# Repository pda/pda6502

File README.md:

pda6502
=======

pda6502 is a home-built computer powered by an 8-bit [6502][6502] CPU
([WDC 65C02][65C02]), varitions of which powered the venerable Commodore 64,
Apple II, Vic 20, Nintendo and lots more.

[74HC-series][7400] logic chips map the 64K address space to 32K RAM, 8K ROM, a
[6522 VIA I/O controller][6522], and room for expansion.

The first output device (beyond flashing LEDs) is a [128x32 pixel OLED][oled],
connected to one of the VIA 6522 parallel ports, with bit-banged serial comms.

It's currently exclusively running the 6502 assembly code which I've written in
the `src/` directory of this project. As of April 2014, it can bit-bang SPI on
the VIA parallel ports to drive the OLED display, rendering text using the old
Commodore 64 font data.

The code is assembled with [ca65][ca65], part of the [cc65][cc65] 6502
development package.

Notes
-----

ILI9340 SPI performance; filling 200x200 square.
baseline: 4.5 seconds.

Emulator
--------

I've also written [go6502][go6502], an emulator for this system.

go6502 features a stepping debugger with breakpoints on instruction type,
register values and memory location. This makes it far easier to get code
working correctly before writing it to an actual EEPROM.

Address layout
--------------

Considerations:

* 6502 has 16-bit address bus; can address 64K memory.
* Zero-page (0x0000..0x00FF) must be RAM, used as external registers.
* Stack (0x0100..0x00FF) must be RAM.
* PC (program counter) is initialized from 0xFFFC, so must be ROM.
* 6522 VIA (I/O) has 4-bit RS (register select), needs 16 bytes mapped.
* AT28C64 EEPROMs are 8kb. I have some.
* Nice to have:
  * Fancy bank-switching (e.g. ROMs overlaying RAM, C64-style).
  * Different mapping for read vs. write, e.g. read ROM, write RAM.

74HC521/74HC688 can route a specific page (256 bytes, upper 8 bits of address)
to a destination. See http://wilsonminesco.com/6502primer/addr_decoding.html

So using the highest three pins of the address bus, the memory space
can be divided down to 8K blocks.

A simple RAM+ROM+IO scheme:
Allows for future extensions e.g. upper 32K RAM, with ROMs and I/O overlaid.

* 0x0000..0x7FFF: 32K RAM, uninterrupted. Contains zero-page and stack.
* 0x8000..0xBFFF: (reserved)
* 0xC000..0xCFFF: 4K I/O (initially only 16 bytes used by 6522 VIA)
* 0xD000..0xDFFF: (reserved)
* 0xE000..0xFFFF: 8K ROM ("kernal" [sic])

Address table for upper 3 bits of address bus:

NOTE: A15 can directly control RAM's CE/OE.
      This means a 74HC138 decoder can run on A12..14
      (With A15 as the '138 active-high enable input)

Address bus 4 KB chunks:

```
     High   Dec  Dec
Seg  Bits    In  Out  Base    Function
------------------------------------------------
  0  0000             0x0000  RAM
  1  0001             0x1000  RAM
  2  0010             0x2000  RAM
  3  0011             0x3000  RAM
  4  0100             0x4000  RAM
  5  0101             0x5000  RAM
  6  0110             0x6000  RAM
  7  0111             0x7000  RAM
  8  1000   000    0  0x8000
  9  1001   100    4  0x9000  IO (VIA) (should be at 0xC000)
  A  1010   010    2  0xA000
  B  1011   110    6  0xB000  ROM (KERNAL) (should be at 0xE000)
  C  1100   001    1  0xC000
  D  1101   101    5  0xD000
  E  1110   011    3  0xE000
  F  1111   111    7  0xF000  ROM (KERNAL)
```

* 74HC138 (3-to-8 decoder)
    * G1 (active-high enable) driven by A15 (only active 0x8000 and above)
    * G2 (active-low enable) permanently LOW/enabled.
    * Inputs A, B, C driven by A12, A13, A14.
    * Output Y4 enables VIA.
    * Output Y6 & Y7 drive KERNAL ROM via AND gate.
* 74HC08 (Quad 2-input AND gates)
    * Input A1, B1 from 74HC138 Y6, Y7, output Y1 to KERNAL ROM CE/OE.
    * Input A2, B2 from phase2, A15, output Y2 to RAM CS/OE.
    * Three spare AND gates.
* 74HC00 (Quad 2-input NAND gates)
    * Input A1, B1 from A15 (as inverter), output Y1 to A2.
    * Input A2, B2 from Y1, phase2 clock, output Y2 to RAM CS/OE.
* VIA 6522
    * CS1 permanently HIGH/active.
    * CS2B to 74HC138 Y4 (LOW/active for `0b1110____`).
    * Data 0..7 to data bus D0..7.
    * Address 0..3 to address bus A0..3.
    * RWB to 6502 RWB.
    * PHI2 to system oscillator, same as 6502.
    * RESB to reset button, same as 6502.
* ROM AT28C64
    * CE and OE both active-low, tied together.
    * CE/OE to 74HC08 Y1, (LOW/active for `0b111_____`)
    * WE permanently HIGH/inactive.
    * I/O 0..7 to data bus D0..7.
    * Address 0..12 to address bus A0..12.
* RAM (32Kx8 CMOS SRAM; UM61256AK-12)
    * CE and OE both active-low, tied together.
    * CE/OE driven by A15+phase2 via 74HC00 (LOW/active for `0b0_______`)
    * WE (active low) to 6502 RWB.
    * Address 0..14 to address bus A0..14.

Zero Page
---------

The zero page (`0x0000..0x00FF`) is frequently used as "external registers".

Note that Some 6502 derivatives dedicate the first few bytes to hardware ports and
control registers, best avoid those? e.g. 6510 in C64 uses at least two.

[6502]: http://en.wikipedia.org/wiki/MOS_Technology_6502
[65C02]: http://en.wikipedia.org/wiki/WDC_65C02
[6522]: http://en.wikipedia.org/wiki/MOS_Technology_6522
[7400]: http://en.wikipedia.org/wiki/List_of_7400_series_integrated_circuits
[oled]: https://www.adafruit.com/products/661
[golang]: http://golang.org/
[go6502]: https://github.com/pda/go6502
[ca65]: http://cc65.github.io/cc65/doc/ca65.html
[cc65]: http://cc65.github.io/cc65/

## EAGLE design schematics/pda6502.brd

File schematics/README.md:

pda6502 schematics
==================

Schematics for pda6502 hardware builds.

Disclaimer: I have no idea what I'm doing.

First iteration is aiming towards a core board for the 6502, 6522, ROM, RAM and
oscillator.  It would connect the power, data bus, address bus, reset lines and
clock lines.  All other functionality (including memory-mapping logic) would be
external via headers.

A 2x10 header exposes the 6522 VIA ports A and B and their control lines.

Notes / TODO
------------

ERRORS:

* A,B,C inputs to 74HC138 reversed!
    * Moves VIA from $C000 to $9000.
    * Moves lower half of kernal ROM from $E000 to $B000.
* 47uF cap footprint too small.
* reset button footprint too small.
* Expansion font too light for silkscreen printing.

Micro B USB socket:
Dangerous Prototypes Eagle library.
Device: CONN-USB-MICRO-B
USB micro-b connector SMT 0.65 mm pitch, 1.45mm from center to PCB edge, Based on TE part number 1981568-1
http://www.mouser.com/ProductDetail/TE-Connectivity-AMP/1981568-1/?qs=zxTme0yW/baAfvOKTKC5hw==

Memory mapping logic
--------------------

* IN:  CPU A12
* IN:  CPU A13
* IN:  CPU A14
* IN:  CPU A15
* IN:  CPU PHI2
* IN:  CPU PHI1O
* IN:  CPU RWB
* OUT: RAM OE+CE
* OUT: ROM OE+CE
* OUT: VIA CS2B

Logic chips:

* 74HC00 (quad NAND) acting as inverter, NAND gate, and AND gate.
* 74HC138 (3-bit decoder) to split the upper-half of address space.

Propagation times:

* 74HC00 gates: typical 8 ns, max 23 ns.
* 74HC138: typical 15 ns, max 38 ns.

* RAM: invert (NAND) + NAND = typical 16 ns, max 46 ns.
* VIA: 74HC138 = typical 15 ns, max 38 ns.
* ROM: 74HC138 + (NAND + NAND) = typical 31 ns, max 84 ns.

* RAM speed: 12 ns
* ROM speed: 250 ns or 120 ns? 150 ns for Atmel AT28C256-15

Power characteristics
---------------------

Designing for maximum of 1A current should be plenty:

[vreg]: http://www.mouser.com/Search/ProductDetail.aspx?R=MC7805CDTRKGvirtualkey58410000virtualkey863-MC7805CDTRKG

```
65C02: 12 mA @ 8 MHz; 1.5 mA per MHz supply current (loaded)
65C22:  4 mA @ 8 MHz; 0.5 mA per MHz supply current (loaded)
28C64: 30 mA max.
SRAM: 200 mA max; 80 mA typical
      ==========
      246 mA max (chips)
      ==========
TFT:  100 mA
uSD:  100 mA (max during writes)
xprot: 60 mA
oled:  20 mA
      ==========
      526 mA
      ==========
```

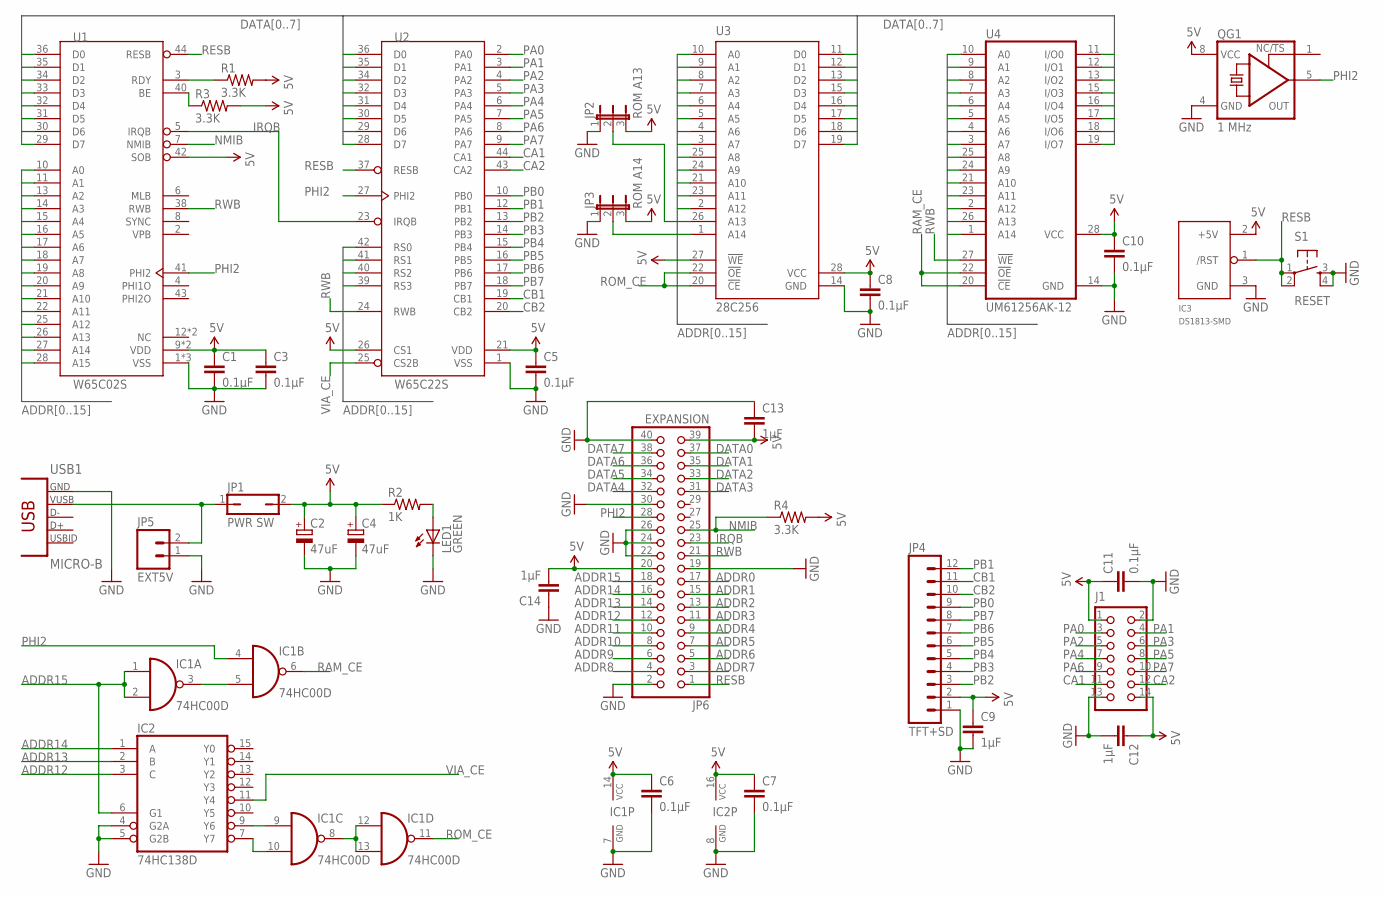
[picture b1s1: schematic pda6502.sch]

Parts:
C1, C3, C5, C6, C7, C8, C10, C11: 0.1μF; C0805
C2, C4: 47uF; CASE_B
C9, C12, C13, C14: 1μF; C0805
IC1: 74HC00D; SO14
IC2: 74HC138D; SO16
IC3: DS1813-SMD; SOT-23
J1: CON_HEADER_2X07-PTH; M2X7
JP1: PWR SW; JMP-1X2
JP2: ROM A13; JP2
JP3: ROM A14; JP2
JP4: TFT+SD; 1X12_NO_SILK_KIT
JP5: EXT5V; 1X02
JP6: EXPANSION; 2X20
LED1: GREEN; LED-805
QG1: 1 MHz; DIL08S
R1, R3, R4: 3.3K; R0805
R2: 1K; R0805
S1: RESET; TACTILE-SWITCH-SMD
U1: W65C02S; PLCC44-SOCKET
U2: W65C22S; PLCC44-SOCKET
U3: 28C256; ZIF28-6-WIDE
U4: UM61256AK-12; DIL28-3
USB1: MICRO-B; CONN_USB_MICRO-B

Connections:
5V: C1.1, C2.+, C3.1, C4.+, C5.1, C6.1, C7.1, C8.1, C9.1, C10.1, C11.1, C12.1, C13.2, C14.2, IC1.14 (VCC), IC2.16 (VCC), IC3.2 (+5V), J1.1, J1.14, JP1.2, JP2.3, JP3.3, JP4.2, JP6.20, JP6.39, QG1.8 (VCC), R1.2, R2.1, R3.2, R4.2, U1.9 (VDD), U1.37 (VDD), U1.42 (SOB), U2.21 (VDD), U2.26 (CS1), U3.27 (!WE), U3.28 (VCC), U4.28 (VCC)
ADDR0: JP6.17, U1.10 (A0), U2.42 (RS0), U3.10 (A0), U4.10 (A0)
ADDR1: JP6.15, U1.11 (A1), U2.41 (RS1), U3.9 (A1), U4.9 (A1)
ADDR2: JP6.13, U1.13 (A2), U2.40 (RS2), U3.8 (A2), U4.8 (A2)
ADDR3: JP6.11, U1.14 (A3), U2.39 (RS3), U3.7 (A3), U4.7 (A3)
ADDR4: JP6.9, U1.15 (A4), U3.6 (A4), U4.6 (A4)
ADDR5: JP6.7, U1.16 (A5), U3.5 (A5), U4.5 (A5)
ADDR6: JP6.5, U1.17 (A6), U3.4 (A6), U4.4 (A6)
ADDR7: JP6.3, U1.18 (A7), U3.3 (A7), U4.3 (A7)
ADDR8: JP6.4, U1.19 (A8), U3.25 (A8), U4.25 (A8)
ADDR9: JP6.6, U1.20 (A9), U3.24 (A9), U4.24 (A9)
ADDR10: JP6.8, U1.21 (A10), U3.21 (A10), U4.21 (A10)
ADDR11: JP6.10, U1.22 (A11), U3.23 (A11), U4.23 (A11)
ADDR12: IC2.3 (C), JP6.12, U1.25 (A12), U3.2 (A12), U4.2 (A12)
ADDR13: IC2.2 (B), JP6.14, U1.26 (A13), U4.26 (A13)
ADDR14: IC2.1 (A), JP6.16, U1.27 (A14), U4.1 (A14)
ADDR15: IC1.1 (I0), IC1.2 (I1), IC2.6 (G1), JP6.18, U1.28 (A15)
CA1: J1.11, U2.44 (CA1)
CA2: J1.12, U2.43 (CA2)
CB1: JP4.11, U2.19 (CB1)
CB2: JP4.10, U2.20 (CB2)
DATA0: JP6.37, U1.36 (D0), U2.36 (D0), U3.11 (D0), U4.11 (I/O0)
DATA1: JP6.35, U1.35 (D1), U2.35 (D1), U3.12 (D1), U4.12 (I/O1)
DATA2: JP6.33, U1.34 (D2), U2.34 (D2), U3.13 (D2), U4.13 (I/O2)
DATA3: JP6.31, U1.33 (D3), U2.32 (D3), U3.15 (D3), U4.15 (I/O3)
DATA4: JP6.32, U1.32 (D4), U2.31 (D4), U3.16 (D4), U4.16 (I/O4)
DATA5: JP6.34, U1.31 (D5), U2.30 (D5), U3.17 (D5), U4.17 (I/O5)
DATA6: JP6.36, U1.30 (D6), U2.29 (D6), U3.18 (D6), U4.18 (I/O6)
DATA7: JP6.38, U1.29 (D7), U2.28 (D7), U3.19 (D7), U4.19 (I/O7)
GND: C1.2, C2.-, C3.2, C4.-, C5.2, C6.2, C7.2, C8.2, C9.2, C10.2, C11.2, C12.2, C13.1, C14.1, IC1.7 (GND), IC2.4 (G2A), IC2.5 (G2B), IC2.8 (GND), IC3.3 (GND), J1.2, J1.13, JP2.1, JP3.1, JP4.1, JP5.1, JP6.2, JP6.19, JP6.22, JP6.24, JP6.26, JP6.30, JP6.40, LED1.C, QG1.4 (GND), S1.3, S1.4, U1.1 (VSS), U1.23 (VSS), U1.24 (VSS), U2.1 (VSS), U3.14 (GND), U4.14 (GND), USB1.P5 (GND)
IRQB: JP6.23, U1.5 (IRQB), U2.23 (IRQB)
unnamed: LED1.A, R2.2
unnamed: IC1.10 (I1), IC2.7 (Y7)
unnamed: IC1.9 (I0), IC2.9 (Y6)
unnamed: JP1.1, JP5.2, USB1.P1 (VUSB)
unnamed: IC1.8 (O), IC1.12 (I0), IC1.13 (I1)
unnamed: JP3.2, U3.1 (A14)
unnamed: IC1.3 (O), IC1.5 (I1)
unnamed: R3.1, U1.40 (BE)
unnamed: R1.1, U1.3 (RDY)
unnamed: JP2.2, U3.26 (A13)
NMIB: JP6.25, R4.1, U1.7 (NMIB)
PA0: J1.3, U2.2 (PA0)
PA1: J1.4, U2.3 (PA1)
PA2: J1.5, U2.4 (PA2)
PA3: J1.6, U2.5 (PA3)
PA4: J1.7, U2.6 (PA4)
PA5: J1.8, U2.7 (PA5)
PA6: J1.9, U2.8 (PA6)
PA7: J1.10, U2.9 (PA7)
PB0: JP4.9, U2.10 (PB0)
PB1: JP4.12, U2.12 (PB1)
PB2: JP4.3, U2.13 (PB2)
PB3: JP4.4, U2.14 (PB3)
PB4: JP4.5, U2.15 (PB4)
PB5: JP4.6, U2.16 (PB5)
PB6: JP4.7, U2.17 (PB6)
PB7: JP4.8, U2.18 (PB7)
PHI2: IC1.4 (I0), JP6.28, QG1.5 (OUT), U1.41 (PHI2), U2.27 (PHI2)
RAM_CE: IC1.6 (O), U4.20 (!CE), U4.22 (!OE)
RESB: IC3.1 (/RST), JP6.1, S1.1, S1.2, U1.44 (RESB), U2.37 (RESB)
ROM_CE: IC1.11 (O), U3.20 (!CE), U3.22 (!OE)
RWB: JP6.21, U1.38 (RWB), U2.24 (RWB), U4.27 (!WE)
VIA_CE: IC2.11 (Y4), U2.25 (CS2B)

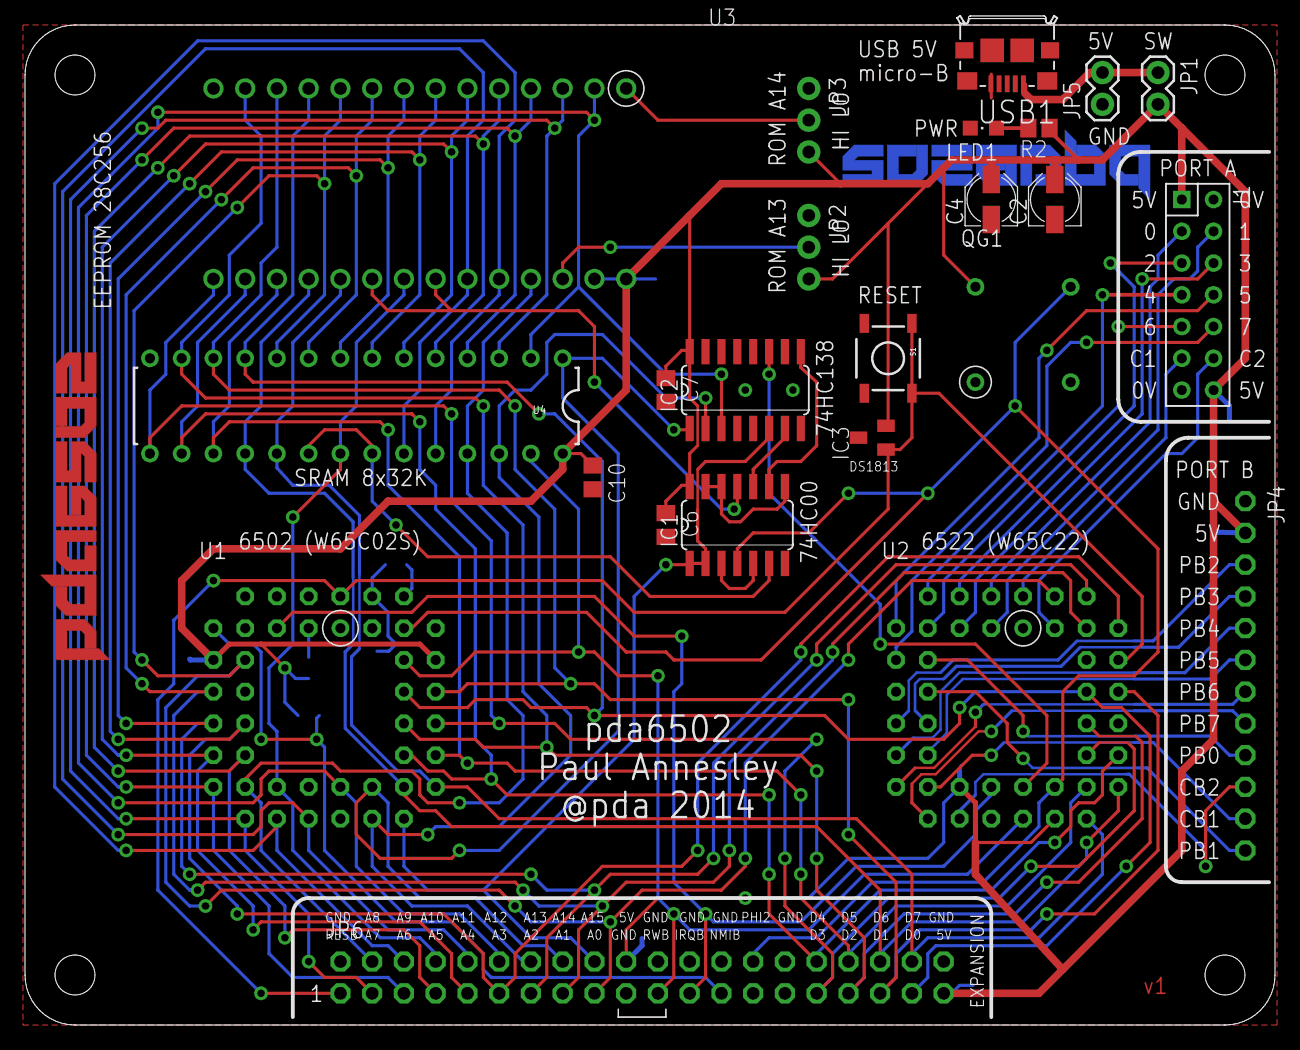
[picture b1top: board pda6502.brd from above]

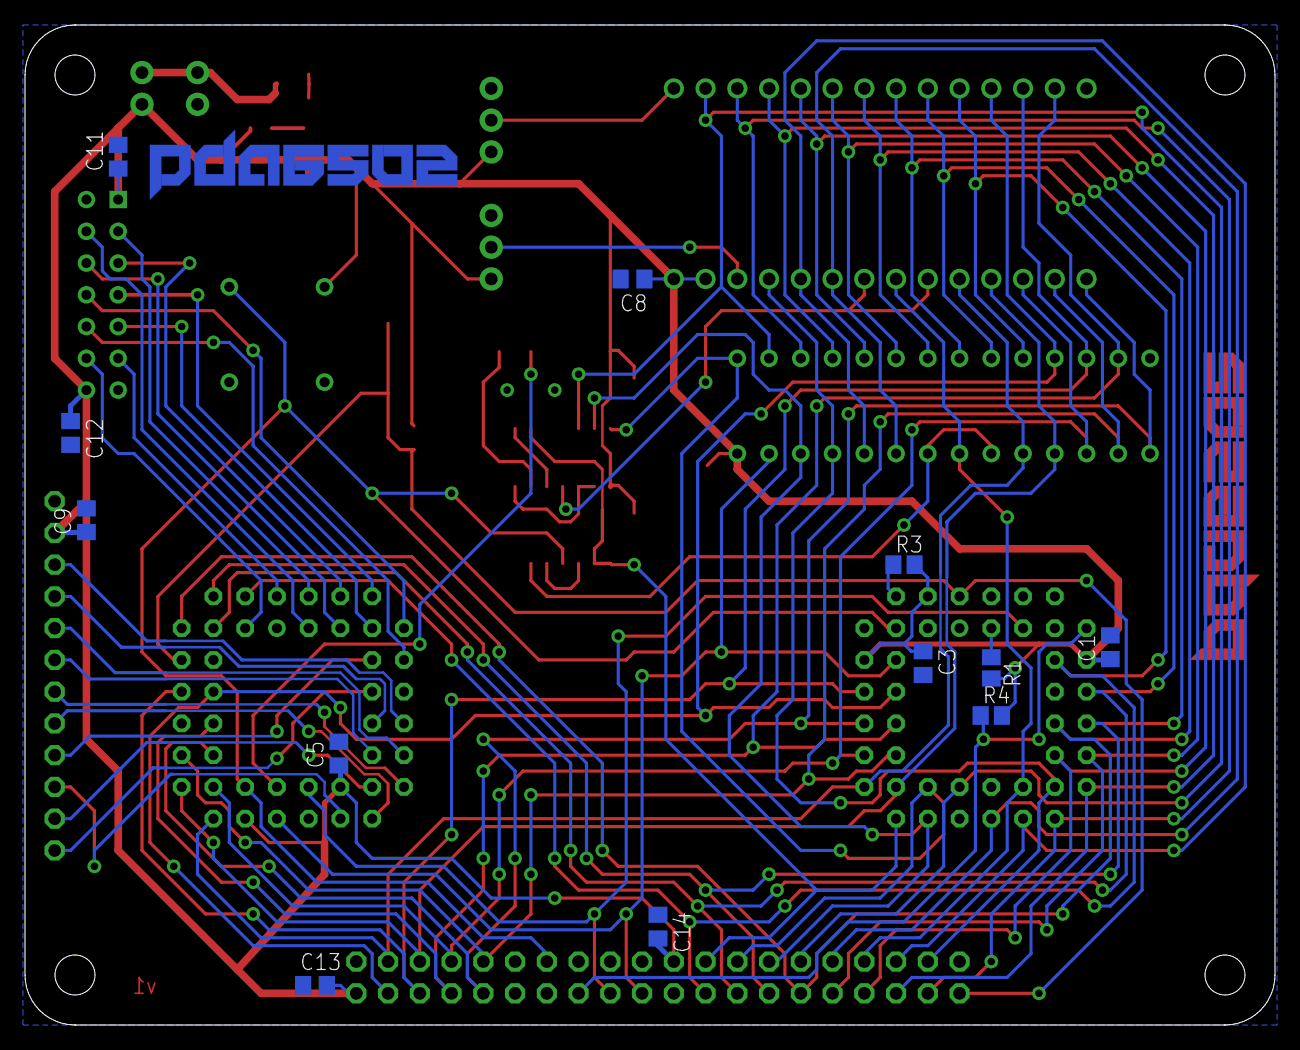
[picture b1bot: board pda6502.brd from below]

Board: 2 copper layers, 100.0 x 80.0 mm, 40 parts (13 on the bottom side), 64 nets.

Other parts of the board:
U$1: DP10080_V1
U$2: ADA-TFT-240X230-22INCH
U$3, U$4: PDA6502-LOGO

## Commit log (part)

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2013-11-29 Initial commit.
2013-11-29 README.
2013-12-17 README updates; address bus design; 32K RAM, VIA I/O, 8K ROM.
2013-12-17 Git ignores *.o and build/*
2013-12-17 Questionable Makefile for ca65 assembler, cl65 linker.
2013-12-17 kernal.rom is 8 KB, starts at 0xE000 (final 8KB).
2013-12-21 Trivial README update re 6522 VIA.
2013-12-21 Whitespace & comments in kernal.s
2013-12-21 Write to 6522 VIA data-direction and output-data registers.
2013-12-25 kernal.s writes a message to VIA 6522 at $C000
2014-04-11 README.md has minimal memory map (ROM+VIA, no RAM).
2014-04-11 README minimal memory table matches main one.
2014-04-12 Working Arduino sketch and python client for EEPROM.
2014-04-12 README pins to address space cruft removed.
2014-04-12 kernal works on actual hardware. Re-indented.
    Tested with 8K segments (A13..15 into 74HC138).
2014-04-12 kernal.s: removed sleep loop.
2014-04-14 kernal.s: flashes SSD1306 OLED display on VIA port A.
2014-04-19 `make burn` has more permissive usbmodem glob.
2014-04-19 kernal.s: load ssd_mask_dc immediate, not absolute.
    This was causing SSD1306 OLED D/C line to be held permanently low,
    meaning data bytes were being interpreted as commands.
2014-04-19 kernal.s writes full 128x32 OLED data, not just half.
2014-04-20 kernal.s: VIA PCR sets both CB2 & CA2 to pulse output.
2014-04-20 `make burn` verifies data.
2014-04-20 kernal.s uses ca65's cheap local @lables.
    http://cc65.github.io/cc65/doc/ca65.html#ss6.5
2014-04-21 SSD1306 moved to VIA port B.
2014-04-21 memory.s: CopyPages; copy X pages from *$10 to *$12.
2014-04-23 font.s imported from subset of C64 character ROM.
2014-04-24 SplashData comment removed; no longer true.
2014-04-24 ShiftZpXLeftByY & ShiftZpXRightByY extracted to bitwise.s
2014-04-24 Deleted splash_data.s (adafruit)
2014-04-24 Write to OLED buffer via ssd1306_ptr.
2014-04-24 Read font data via font_ptr.
2014-04-26 OLED says "HELLO WORLD! - PDA6502".
2014-04-26 FontSelectChar in new font.s
2014-04-26 Ssd1306WriteCharacter subroutine extracted.
2014-04-26 FontSelectChar overhauled, fully 16-bit.
2014-04-26 encoding.s exports AsciiToPetscii.
2014-04-26 Display multiple "@" using SsdNextSegment.
2014-04-26 font_data.s has entire 4K from C64 character ROM.
2014-04-26 Ssd1306WriteCharacter fixed; renders 8th column of pixels.
2014-04-26 AsciiToPetscii maps $00..$1F to decorative chars.
2014-05-01 AsciiToPetscii corrected; SBC/BCS/BCC was wrong.
    > If you’re not used to 65x processors (and even for many programmers who
    > are), you may tend to write an ADC instruction without first writing a
    > CLC, or an SBC without first an SEC.
    -- WDC programmer manual
2014-05-14 WIP: SD card support.
2014-05-20 sd: deselect chip during init (SS=HIGH).
2014-05-20 sd: SpiByte loop comparison simpler (DEY, not INY+CPY).
2014-05-25 sd: sdCardCommandZeroArg sets CMD upper bits correctly.
2014-05-25 sd: SdCardRead (first block only, into $6000).
2014-05-25 ssd1306: missing RTS for Ssd1306WriteScreen.
2014-05-25 Ssd1306WriteScreen takes buffer address via X,Y.
2014-05-26 Main sleeps 1 second then displays message from SD card.
2014-06-04 memory.conf URLs corrected to cc65.github.io
2014-06-04 memory.conf: long declarations split across lines.
2014-06-09 memory.conf: kernal_bss segment at $0800.
2014-06-09 ssd1306: configureSpi for SpiByte; not yet used.
2014-06-12 Boot screen says PDA6502 READY etc, was HELLO WORLD.
2014-06-12 sd.s: SD CMD args via user stack internally.
2014-06-16 kernal.s: roughly extracted splashScreen subroutine.
2014-06-16 kernal.s: display SD data from two different blocks.
    $00000000 is first 512-byte block on card.
    $00000200 is second 512-byte block on card.
    This proves that multiple blocks can be read from SD; i.e. reading a
    block doesn't leave sd.s in a broken state.
2014-06-16 sd: SdCardRead reads full 512-byte block.
    Previously only 256 bytes were read, leaving it in a broken state;
    the card was expecting to send more data, the code in sd.s was expecting
    to be able to send the next command.
2014-06-20 kernal: loadSplashScreen loads into $6000 for displayText.
    Previously it had its own displayText-like implementation.
2014-06-20 fat: WIP; read FAT32 params from SD card into kernal_bss vars.
    Testing with:
    go6502 -via-ssd1306 -sd-card=sd4gb.fat32 \
    -debug -debug-symbol-file=build/debug \
    -debug-commands="
    break-address Halt;
    continue;
2014-06-21 fat: calculateFatOffset derives FatFatOffset.
    Assumes 512-byte sector size.
2014-06-21 fat: calculateFatTotalSize derives FatFatTotalSize.
2014-06-21 fat: calculateClusterSize derives FatClusterSize.
2014-06-25 fat: FatDataAddress for cluster zero, not cluster one.
    As described, cluster #0 and cluster #1 may not be accessed, and this
    FatDataAddress actually points to an address before the data region.
2014-06-25 fat: delete unused readSecondBlock subroutine.
2014-06-25 kernal: read FAT32 root directory from SD card into RAM.
2014-06-25 fat: FatReadFile, with FatSearchFilename BSS var as param.
2014-06-25 kernal: Display text from SPLASH.TXT on FAT32 SD card.
    Tested in go5602 emulator, not on hardware.
2014-08-09 pda.lbr Eagle library with W65C02S (6502)
2014-08-09 schematics/README.md
2014-08-09 schematics: DIP28-SKIINNY in library.
2014-08-11 schematics: .gitignore separated from main .gitignore
2014-08-11 schematics: use parts newly imported into library.
2014-08-11 schematics: use 28C64 newly added to library.
2014-08-11 schematics: 28C64 in library.
2014-08-11 schematics: README.md updates
2014-08-11 schematics: schematic component spacing / orientation tweaked.
2014-08-11 schematics: RWB connected 6502, 6522, RAM. Split named net.
2014-08-11 schematics: OE and CE tied together, for ROM and RAM.
2014-08-11 schematics: reset circuit (DS1813); no button yet.
2014-08-11 schematics: reset circuit has button.
2014-08-11 schematics: crystal oscillator; half can.
2014-08-11 schematics: VIA CS1 tied high (active). See active-low CS2B.
2014-08-11 schematics: PHI2 net into 6502 fixed; was not connected.
2014-08-11 schematics: PLCC44-SOCKET in library.
2014-08-11 schematics: RAM package updated to fixed DIL28-3.
2014-08-11 schematics: 6502 in PLCC44 package.
2014-08-11 schematics: W65C02 naming corrections / tweaks.
2014-08-11 schematics: 6522 in PLCC44 socket package.
2014-08-20 schematics: EAGLE version="7.1.0", was 7.0.0
2014-08-20 schematics: ZIF28-6-WIDE in library.
2014-08-20 schematics: 28C64 ROM uses ZIF socket package.
2014-08-20 schematics: approximate power characteristics in README.
2014-08-20 schematics: TO-263-D2PAK package in library.
2014-08-20 schematics: L7805-VREG-D2PAK device in library.
2014-08-21 schematics: 7805 regulator package swapped to TO252 (DPAK).
2014-08-21 schematics: L7805-VREG-D2PAK removed from library.
    Using standard library parts for 7805 regulator.
2014-08-21 schematics: deleted voltage regulator; assume 5VDC input.
    A switching mode 5V DC wall adapter should be fine.
2014-08-23 schematics: micro USB power supply.
2014-08-23 schematics: compacted schematic layout.
2014-08-23 schematics: no more 40-pin expansion socket.
2014-08-23 schematics: parts auto-renumbered.
2014-08-23 schematics: README describes logic chips, timing.
2014-08-23 schematics: 28C256 symbol with ZIF-package device in library.
2014-08-23 schematics: rearranged; memory mapping bottom right, PSU bottom left.
2014-08-24 schematics: compacted PSU schematic, and clock circuit.
2014-08-24 schematics: removed 2x10 VIA header (PA + PB).
2014-08-24 schematics: VIA exposes two 2x7 headers; port A and port B.
2014-08-24 schematics: TFT+SD header, plus schematic layout changes.
2014-08-24 schematics: TFT+SD header on PORTB for shift-register.
    SR used as PWM to control backlight.
2014-08-28 schematics: PORTB hdr changed, 40-pin hdr is back.
2014-08-28 board: components tentatively placed, no routing.
2014-08-28 board: routed OE and CE to each other on RAM and ROM.
2014-08-28 board: routed decoupling caps to power pins, etc.
2014-08-31 board: alternate grid set to 0.005 as per SparkFun article.
2014-08-31 board: layout tweaks; oscillators and memory mapping.
2014-08-31 board: WIP; power routing.
2014-08-31 schematics: ERC fixes; expansion header has decoupling cap.
    (Does the cap even make sense there? The more the merrier...)
2014-09-01 board: routing WIP; thick power traces, reaching more devices.
2014-09-02 board: 6522 VIA PORTB routed.
2014-09-02 board: USB socket closer to edge; routing adjusted.
2014-09-03 board: routing WIP: 5V edge lines shifted in.
2014-09-03 board: routed expansion port DATA to 6522.
2014-09-03 board: further routing, placement adjustments.
2014-09-06 board: PORTB bumped north; fine trace width normalized, tweaks.
2014-09-06 board: routed ADDR[0..7, 12] down left side of board.
2014-09-06 board: 6502 moved 50 mils left; more space in center.
2014-09-06 board: more routing from 6502 to memory.
2014-09-06 board: routed PHI2; 30 airwires.
2014-09-10 board: routing WIP; 74xx chips on bottom layer.
2014-09-10 board: SMD logic chips routed; top layer of board.
2014-09-10 board: 6502 bumped 50 mils right; left-side traces straightened.
2014-09-13 board: clearance to right of 6502 for ground pour.
2014-09-13 board: 6 airwires; likely all GND plane issues.
2014-09-13 board: vias under RAM adjusted; 3 airwires remaining.
2014-09-13 board: main power re-routed; more ground plane. 0 airwires!
2014-09-13 board: USB connector bumped down for edge alignment.
2014-09-13 board: capacitor orientation consistency; ROM, RAM, 74HC.
2014-09-13 board: capacitor orientation consistency on VIA ports.
2014-09-14 board: alternate grid of 0.025 inch, not 0.005.
    This makes the alternate grid just half, not a fifth, of the primary.
    When necessary, it can be temporarily changed to 0.005.
    This has been the case for most of the work leading up to this commit.
2014-09-18 board: layout tweaks; clock, reset, power LED etc.
2014-09-18 board: power caps have greater clearance from edge.
2014-09-18 board: removed redundant pair of vias; bottom right.
2014-09-21 library: jumpers, and outline of Adafruit TFT board.
2014-09-23 board: many layout / routing adjustments.
    In particular, expansion port has been shifted down closer to edge.
2014-09-23 board: tweaks; USB bumped one mil, power LED moved.
2014-09-24 schematics, board: show grid as lines, not dots.
2014-09-24 board: PDA6502-LOGO next to 6502.
2014-09-24 board: PDA6502-LOGO on bottom also; near USB connector.
2014-10-04 schematics, board: labelling WIP, bigger caps.
2014-10-05 SSD1306 moved to VIA PORTA, was PORTB.
    Now sharing a port with the SD card.
2014-10-07 On boot, write blue to ILI9340 TFT forever (very very slowly).
    At 1 MHz it takes about a minute or two to fill the screen!
2014-10-07 ili9340: set screen to 200x200 with unused margins; loop fixed.
2014-10-16 logo from 99designs contest.
    As uploaded by the designer in AI, EPS, JPH, PDF and PNG formats, with
    white background and black background.
    http://99designs.com/logo-design/contests/pda-retro-hobby-electronics-logo-415054
2014-10-19 schematics, board: labelling, tweaks, polish.
2014-10-20 board: labelling, layout tweaks, polish.
2014-10-21 board: spaced routing between PLCCs; more ground pour.
2014-10-21 board: routing minor tweaks; ROM, 74HC00, ...
2014-10-21 board: minor tweaks to keep text off vias.
2014-10-21 board, library: pda6502 has tStop layer, not tCream.
2014-10-22 schematics, board: v1 gerber files as submitted to Seeed.
2014-10-25 ili9340: test pattern; color based on x:y, not solid blue.
2014-10-25 spi: SpiByteReadPortB; MOSI only, no MISO; ~25% faster.
2014-12-03 cc65 upgrade fixes; ~ (.BITNOT) results cast with < (.HIBYTE)
    In cc65 2.13.3 it was valid to use e.g. #~1 in an 8-bit context, but in
    cc65 revision fed3179d3b180ca05ca5ad5037b06e7612d5459f it is rejected
    as out of range unless cast with < or .LOBYTE e.g. #<~1
    Example code and error:
    mask_miso = %10000000
    AND #~(mask_miso)
2014-12-06 memory.conf, Makefile, font_data.s remap rom_lo.
    Due to V1 hardware error on 74HC138 inputs.
2014-12-14 Trimmed kernal.s; preparing for boot loader.

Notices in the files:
parts and their libraries:
SparkFun-Connectors: Licensing: Creative Commons ShareAlike 4.0 International - https://creativecommons.org/licenses/by-sa/4.0
